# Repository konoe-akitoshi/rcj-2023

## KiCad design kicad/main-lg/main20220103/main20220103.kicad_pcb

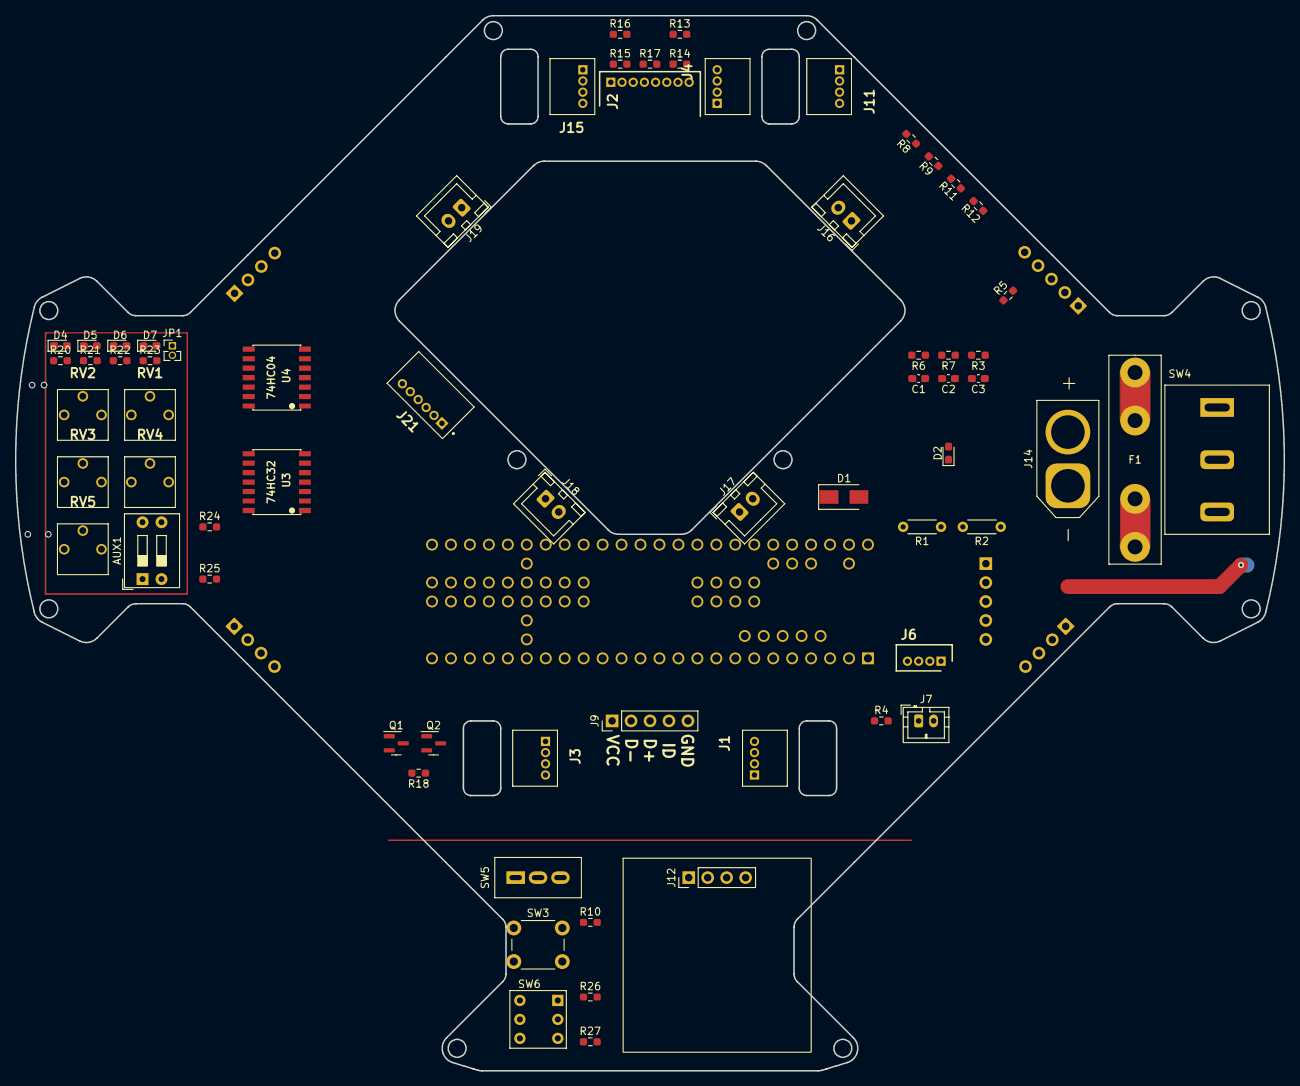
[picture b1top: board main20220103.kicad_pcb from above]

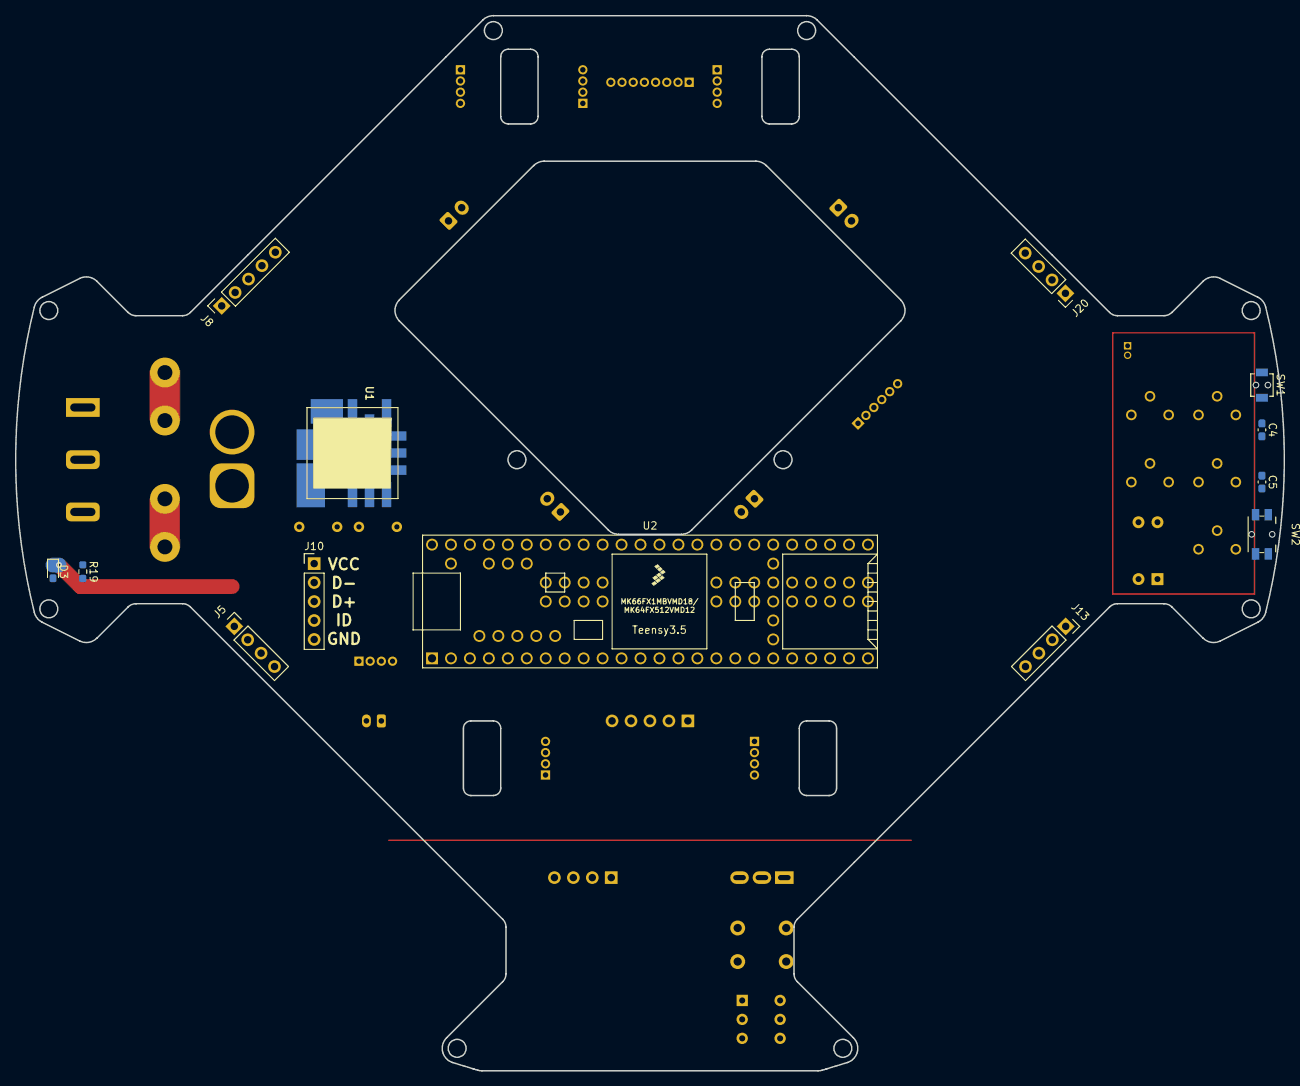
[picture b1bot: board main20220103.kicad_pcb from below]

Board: 2 copper layers, 170.0 x 141.4 mm, 80 parts (13 on the bottom side), 89 nets.

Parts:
AUX1: SW_DIP_x02; SW_DIP_SPSTx02_Slide_9.78x7.26mm_W7.62mm_P2.54mm
C1, C2, C3: 10u; C_0603_1608Metric_Pad1.08x0.95mm_HandSolder
C4, C5: 0.1u; C_0603_1608Metric_Pad1.08x0.95mm_HandSolder
D1: SX34F; D_SMA
D2, D3: LED; LED_SMLE13WBC8W1
D4: LED1_R; LED_SMLE13WBC8W1
D5: LED2_G; LED_SMLE13WBC8W1
D6: LED3_Y; LED_SMLE13WBC8W1
D7: LED4_B; LED_SMLE13WBC8W1
F1: Fuse 15A; FUSE_20mm
J1: MD2; JSTS4B-ZRLFSN
J2: MD4; JSTS4B-ZRLFSN
J3: MD3; JSTS4B-ZRLFSN
J4: MD1; JSTS4B-ZRLFSN
J5: XBee; PinSocket_1x04_P2.54mm_Vertical
J6: Serial3/Vision; JSTB4B-ZR
J7: raspi-power; JST_PH_B2B-PH-K_1x02_P2.00mm_Vertical
J8: Serial2/IMU; PinSocket_1x05_P2.54mm_Vertical
J9: micro-b_out; PinHeader_1x05_P2.54mm_Vertical
J10: micro-b_in; PinHeader_1x05_P2.54mm_Vertical
J11: I2C_ToF; JSTS4B-ZRLFSN
J12: I2C_OLED; OLED
J13: drib-kick; PinSocket_1x04_P2.54mm_Vertical
J14: Power IN; AMASS_XT60-M_1x02_P7.20mm_Vertical
J15: LINE; JSTS8B-ZRLFSN
J16: MD1; JST_XH_B2B-XH-A_1x02_P2.50mm_Vertical
J17: MD2; JST_XH_B2B-XH-A_1x02_P2.50mm_Vertical
J18: MD3; JST_XH_B2B-XH-A_1x02_P2.50mm_Vertical
J19: MD4; JST_XH_B2B-XH-A_1x02_P2.50mm_Vertical
J20: Drib-Kick; PinSocket_1x04_P2.54mm_Vertical
J21: Trimmer; JSTS6B-ZRLFSN
JP1: Jumper_2_Bridged; PinHeader_1x02_P1.27mm_Vertical
Q1: AO3400A; SOT-23
Q2: AO3401A; SOT-23
R1: 1k; R_Axial_DIN0204_L3.6mm_D1.6mm_P5.08mm_Horizontal
R2: 330; R_Axial_DIN0204_L3.6mm_D1.6mm_P5.08mm_Horizontal
R3, R26, R27: 470; R_0603_1608Metric_Pad0.98x0.95mm_HandSolder
R4, R5, R7, R11, R12, R13, R14, R15, R16, R17, R18: 10k; R_0603_1608Metric_Pad0.98x0.95mm_HandSolder
R6, R8, R9, R10, R24, R25: 47k; R_0603_1608Metric_Pad0.98x0.95mm_HandSolder
R19: 3k; R_0603_1608Metric_Pad0.98x0.95mm_HandSolder
R20, R21, R22, R23: 120; R_0603_1608Metric_Pad0.98x0.95mm_HandSolder
RV1, RV2, RV3, RV4, RV5: 20K; Trim-GF063P
SW1: PROG; TVAF06-A020B-R
SW2: Reset; THAU13-AB-R
SW3: SET; SW_PUSH_6mm
SW4: SW_SPST; SW_SPST_POWER
SW5: GOAL; MFS101D-14-Z
SW6: START; SW_NKK_B-12CCPRM
U1: OKL-T_3-W12N-C; OKL-T3-W12N-C
U2: Teensy3.5; Teensy35_36_x
U3: 74HC32; SOP14W
U4: 74HC04; SOP14W

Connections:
+3V3: J15.7, R8.1, R9.1, R11.1, R12.1, R24.1, R25.1, SW5.1 (A), SW6.1 (A), SW6.5 (A), U2.51 (3.3V), U3.14 (VCC), U4.13, U4.14 (VCC)
+5V: C2.1, D1.2 (A), J5.2, J6.2, J7.1, J8.3, J11.2, J12.2, Q2.2 (S), R3.1, R10.1, R18.1, U1.4 (VOUT), U1.5 (SENSE)
+15V: C1.1, F1.1, J16.1, J17.1, J18.1, J19.1, J20.1, J20.3, R6.1, R19.1, U1.2 (VIN)
/AUX1/3: AUX1.3, R24.2, U2.68 (41)
/AUX1/4: AUX1.4, R25.2, U2.67 (40)
/LED/LED1: R20.1, U2.50 (23_A9_PWM_Touch)
/LED/LED2: R21.1, U2.49 (22_A8_PWM_Touch)
/LED/LED3: R22.1, U2.48 (21_A7_PWM_CS0_MOSI1)
/LED/LED4: R23.1, U2.47 (20_A6_PWM_CS0_SCK1)
/Switch/SW_GOAL: SW5.2 (B), U2.41 (14_A0_PWM_SCK0)
/Switch/SW_START: SW6.2 (B), U2.43 (16_A2_SCL0_Touch)
/Switch/SW_led_G: R27.1, U2.44 (17_A3_SDA0_Touch)
/Switch/SW_led_R: R26.1, U2.42 (15_A1_CS0_Touch)
GND: AUX1.1, AUX1.2, C1.2, C2.2, C3.2, C4.2, C5.1, D2.1 (K), D3.1 (K), J5.4, J6.4, J7.2, J8.5, J11.4, J12.4, J13.2, J13.4, J14.1, J15.8, J16.2, J17.2, J18.2, J19.2, J20.2, J20.4, JP1.1 (A), Q1.2 (S), R2.1, R7.2, SW1.2, SW2.2, SW3.2, SW5.3 (C), SW6.3 (C), U1.1 (ON/OFF), U1.3 (GND_1), U1.7 (GND_2), U2.1 (GND), U2.27 (GND), U2.39 (GND), U2.61 (GND), U2.62 (GND), U2.63 (G), U2.74 (GND), U3.7 (GND), U4.7 (GND)
unnamed: C5.2, R9.2, SW2.1, U2.29 (Reset)
unnamed: D1.1 (K), U2.53 (Vin)
unnamed: D2.2 (A), R3.2
unnamed: D3.2 (A), R19.2
unnamed: D4.1 (K), D5.1 (K), D6.1 (K), D7.1 (K), JP1.2 (B)
unnamed: D4.2 (A), R20.2
unnamed: D5.2 (A), R21.2
unnamed: D6.2 (A), R22.2
unnamed: D7.2 (A), R23.2
unnamed: F1.2, SW4.1 (A)
unnamed: J1.1, J1.3, U2.33 (36_A17_PWM)
unnamed: J1.2, U2.72 (45_MISO2)
unnamed: J1.4, U2.73 (46_SCK2)
unnamed: J2.1, J2.3, U2.35 (38_A19_PWM_SDA1)
unnamed: J2.2, U2.78 (49_A23)
unnamed: J2.4, U2.79 (50_A24)
unnamed: J3.1, J3.3, U2.34 (37_A18_PWM_SCL1)
unnamed: J3.2, U2.76 (47_RX6_SCL0)
unnamed: J3.4, U2.77 (48_TX6_SDA0)
unnamed: J4.1, J4.3, U2.32 (35_A16_PWM)
unnamed: J4.2, U2.70 (43_CS2)
unnamed: J4.4, U2.71 (44_MOSI2)
unnamed: J5.1, U2.3 (1_TX1_MISO1_Touch)
unnamed: J5.3, U2.2 (0_RX1_MOSI1_Touch)
unnamed: J6.1, U2.10 (8_TX3_MISO0_SDA0)
unnamed: J6.3, R4.2
unnamed: J8.1, R10.2, SW3.1
unnamed: J8.2, U2.12 (10_PWM_TX2_CS0)
unnamed: J8.4, R5.2
unnamed: J9.1, J10.1
unnamed: J9.2, J10.2
unnamed: J9.3, J10.3
unnamed: J9.4, J10.4
unnamed: J9.5, J10.5
unnamed: J11.1, J12.1, R11.2, U2.46 (19_A5_SCL0_Touch)
unnamed: J11.3, J12.3, R12.2, U2.45 (18_A4_SDA0_Touch)
unnamed: J13.1, U2.8 (6_PWM)
unnamed: J13.3, U2.13 (11_MOSI0)
unnamed: J14.2, SW4.2 (B)
unnamed: J15.1, R13.2
unnamed: J15.2, R14.2
unnamed: J15.3, R17.2
unnamed: J15.4, Q2.3 (D)
unnamed: J15.5, R15.2
unnamed: J15.6, R16.2
unnamed: J21.1, RV1.1, RV2.1, RV3.1, RV4.1, RV5.1
unnamed: J21.2, RV5.2, RV5.3
unnamed: J21.3, RV4.2, RV4.3
unnamed: J21.4, RV3.2, RV3.3
unnamed: J21.5, RV2.2, RV2.3
unnamed: J21.6, RV1.2, RV1.3
unnamed: Q1.1 (G), U2.22 (30_PWM_CAN0RX_Touch)
unnamed: Q1.3 (D), Q2.1 (G), R18.2
unnamed: R1.1, R2.2
unnamed: R1.2, U1.6 (TRIM)
unnamed: R4.1, U2.9 (7_RX3_MOSI0_SCL0)
unnamed: R5.1, U2.11 (9_PWM_RX2_CS0)
unnamed: R13.1, U2.37 (A21_DAC0), U4.1
unnamed: R14.1, U2.38 (A22_DAC1), U4.3
unnamed: R15.1, U2.59 (A26_D-), U4.9
unnamed: R16.1, U2.36 (39_A20), U4.11
unnamed: R17.1, U2.60 (A25_D+), U4.5
unnamed: R26.2, SW6.4 (KR)
unnamed: R27.2, SW6.6 (KG)
unnamed: U2.16 (24), U3.4, U4.2
unnamed: U2.17 (25), U3.9, U4.4
unnamed: U2.18 (26_TX1_SCL2), U3.5, U4.6
unnamed: U2.19 (27_RX1_SCK0), U3.10, U4.8
unnamed: U2.20 (28_MOSI0), U3.1, U4.10
unnamed: U2.21 (29_PWM_CAN0TX_Touch), U3.3
unnamed: U3.2, U3.11
unnamed: U3.6, U3.12
unnamed: U3.8, U3.13
PROG: C4.1, R8.2, SW1.1, U2.28 (Program)
Vbatt: C3.1, R6.2, R7.1, U2.30 (33_A14_TX5_CAN1TX_SCL0)

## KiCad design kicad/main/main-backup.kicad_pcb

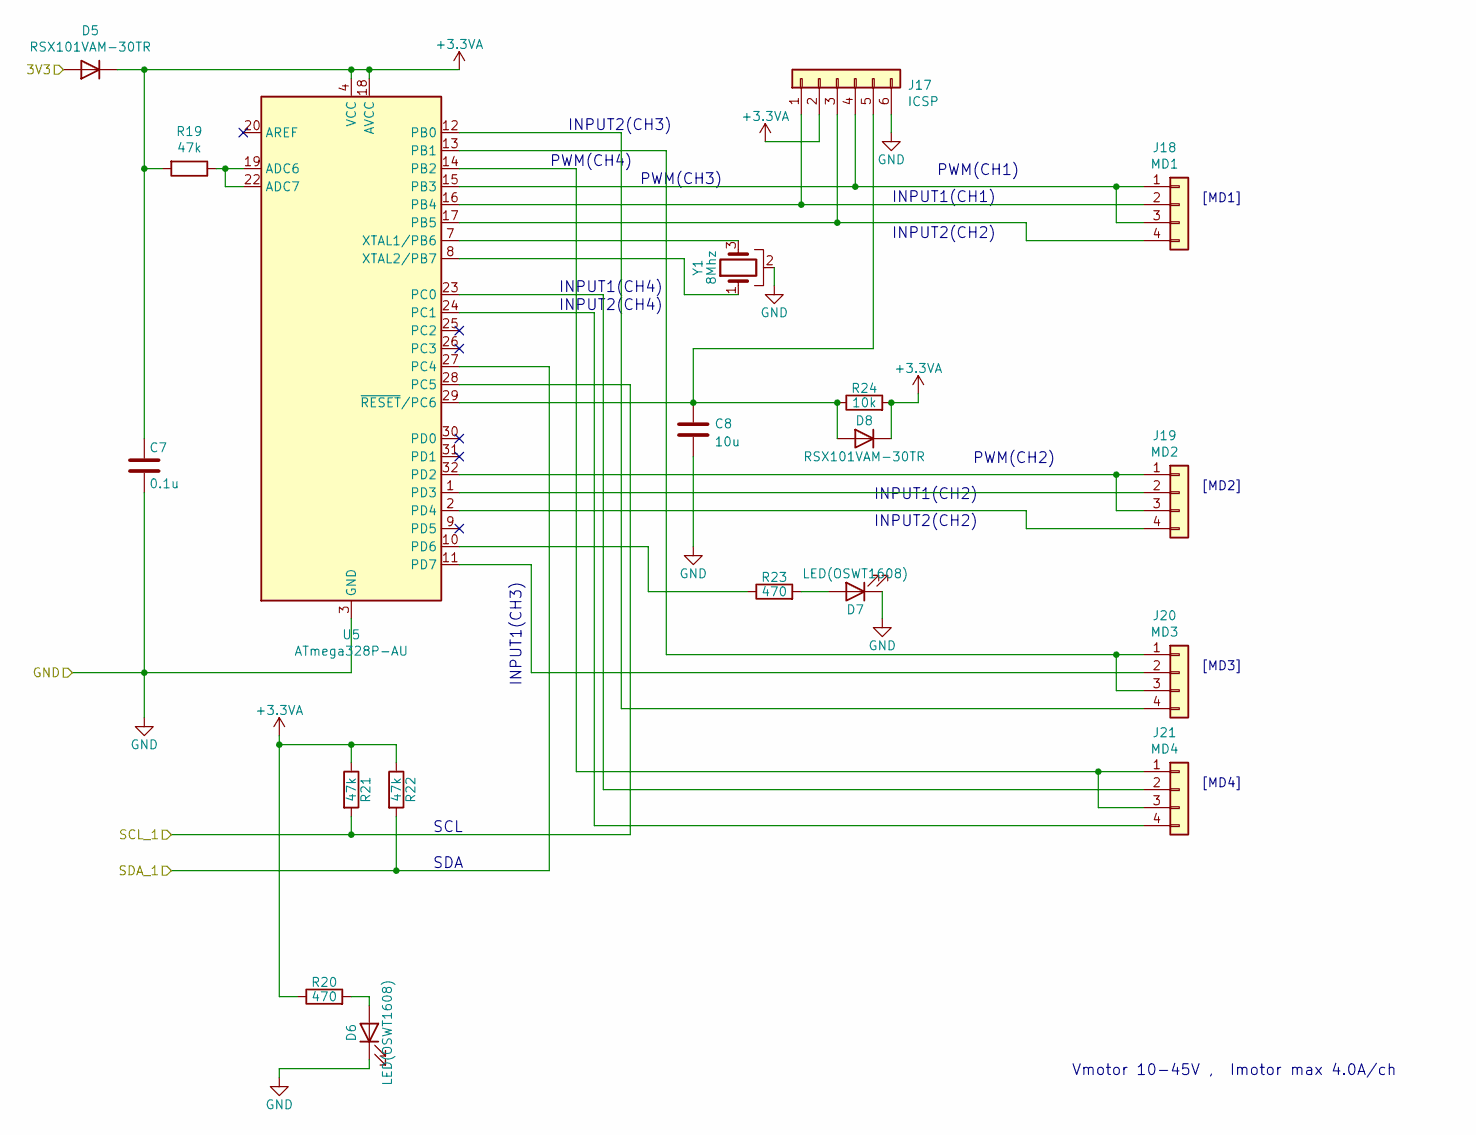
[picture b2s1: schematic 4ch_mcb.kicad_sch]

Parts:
C7: 0.1u; C_0603_1608Metric_Pad1.08x0.95mm_HandSolder
C8: 10u; C_0603_1608Metric_Pad1.08x0.95mm_HandSolder
D5, D8: RSX101VAM-30TR; D_0805_2012Metric_Pad1.15x1.40mm_HandSolder
D6, D7: LED(OSWT1608); LED_0603_1608Metric_Pad1.05x0.95mm_HandSolder
J17: ICSP; JSTB6B-ZR
J18: MD1; JSTB4B-ZR
J19: MD2; JSTB4B-ZR
J20: MD3; JSTB4B-ZR
J21: MD4; JSTB4B-ZR
R19, R21, R22: 47k; R_0603_1608Metric_Pad0.98x0.95mm_HandSolder
R20, R23: 470; R_0603_1608Metric_Pad0.98x0.95mm_HandSolder
R24: 10k; R_0603_1608Metric_Pad0.98x0.95mm_HandSolder
U5: ATmega328P-AU; TQFP-32_7x7mm_P0.8mm
Y1: 8Mhz; Resonator-3Pin_W6.0mm_H3.0mm

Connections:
+3.3VA: C7.1, D5.1 (K), D8.1 (K), J17.2, R19.2, R20.1, R21.1, R22.1, R24.2, U5.4 (VCC), U5.6 (VCC), U5.18 (AVCC)
/Sheet63625160/SCL_1: R21.2, U5.28 (PC5); also elsewhere on the board
/Sheet63625160/SDA_1: R22.2, U5.27 (PC4); also elsewhere on the board
unnamed: C8.1, D8.2 (A), J17.5, R24.1, U5.29 (~RESET/PC6)
unnamed: D6.2 (A), R20.2
unnamed: D7.2 (A), R23.2
unnamed: J17.1, J18.2, U5.16 (PB4)
unnamed: J17.3, J18.4, U5.17 (PB5)
unnamed: J17.4, J18.1, J18.3, U5.15 (PB3)
unnamed: J19.1, J19.3, U5.32 (PD2)
unnamed: J19.2, U5.1 (PD3)
unnamed: J19.4, U5.2 (PD4)
unnamed: J20.1, J20.3, U5.13 (PB1)
unnamed: J20.2, U5.11 (PD7)
unnamed: J20.4, U5.12 (PB0)
unnamed: J21.1, J21.3, U5.14 (PB2)
unnamed: J21.2, U5.23 (PC0)
unnamed: J21.4, U5.24 (PC1)
unnamed: R19.1, U5.19 (ADC6), U5.22 (ADC7)
unnamed: R23.1, U5.10 (PD6)
unnamed: U5.7 (XTAL1/PB6), Y1.3
unnamed: U5.8 (XTAL2/PB7), Y1.1
SW1_3: D5.2 (A); also elsewhere on the board
SW1_6: C7.2, C8.2, D6.1 (K), D7.1 (K), J17.6, U5.3 (GND), U5.5 (GND), U5.21 (GND), Y1.2; also elsewhere on the board

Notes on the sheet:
INPUT2(CH3)
INPUT2(CH2)
PWM(CH1)
PWM(CH3)
PWM(CH2)
INPUT1(CH2)
INPUT1(CH4)
[MD2]
INPUT1(CH3)
[MD4]
INPUT2(CH4)
PWM(CH4)
[MD1]
SDA
[MD3]
Vmotor 10-45V , Imotor max 4.0A/ch
SCL
INPUT1(CH1)

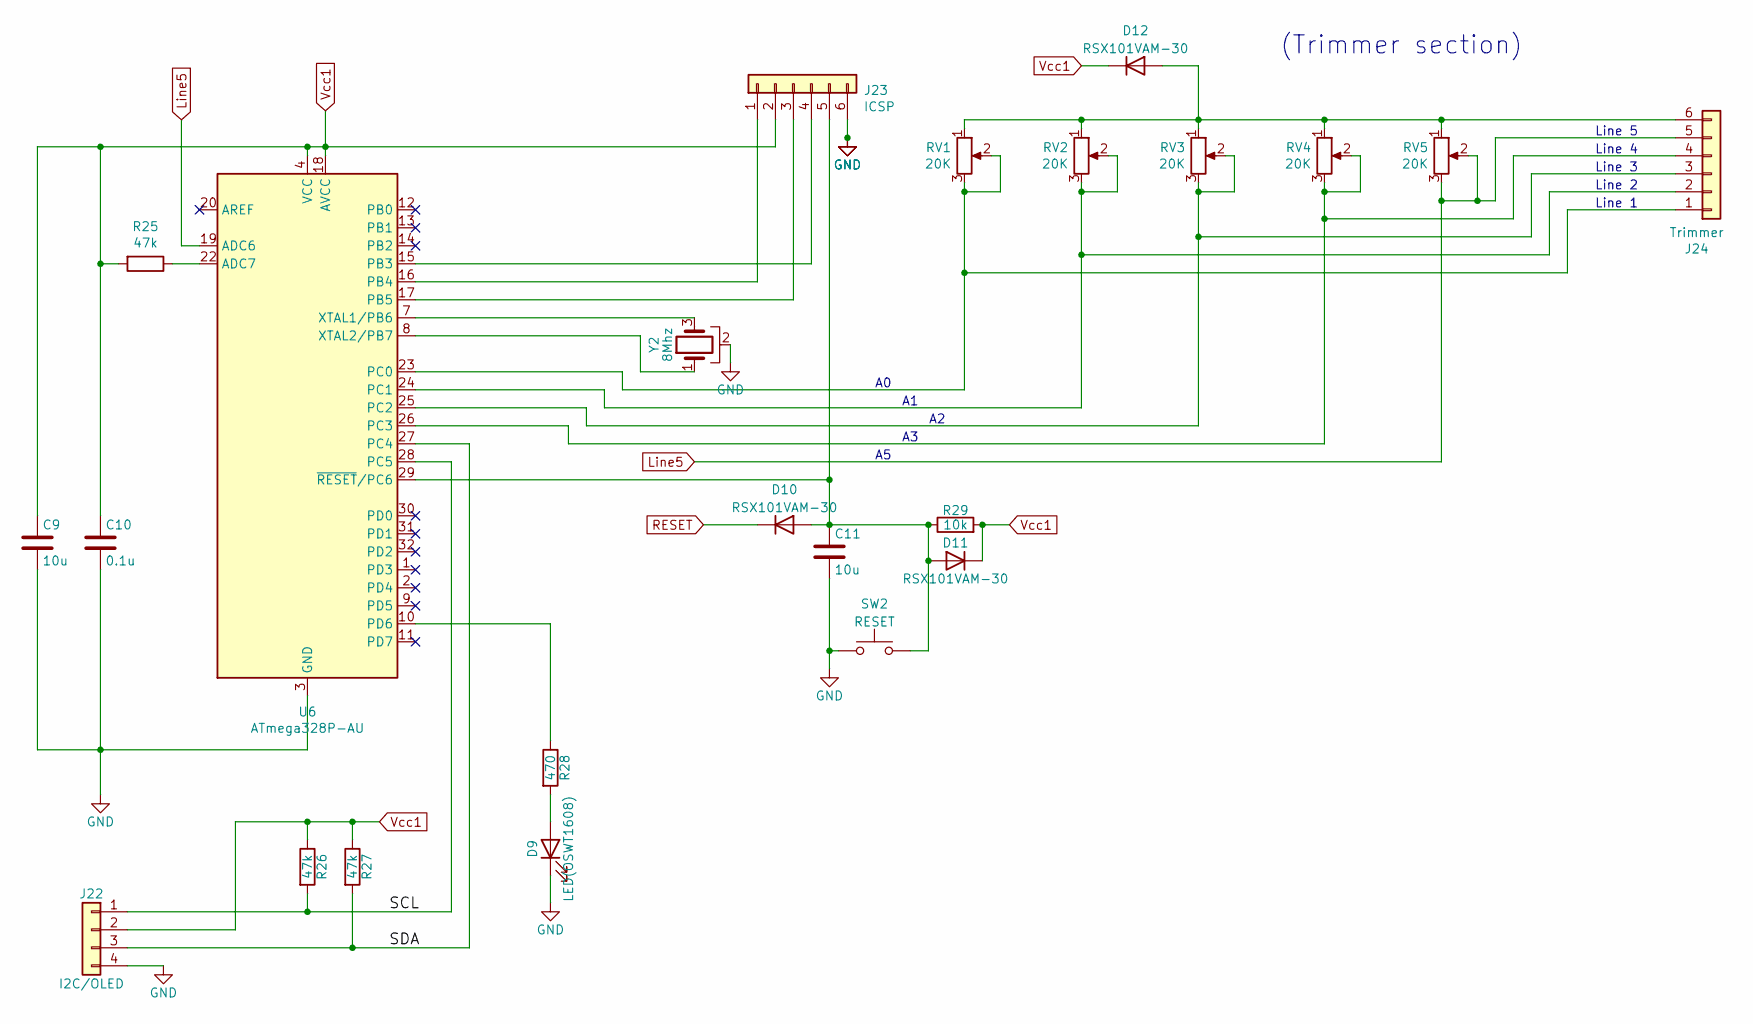
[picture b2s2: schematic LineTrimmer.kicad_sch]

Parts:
C9, C11: 10u; C_0603_1608Metric_Pad1.08x0.95mm_HandSolder
C10: 0.1u; C_0603_1608Metric_Pad1.08x0.95mm_HandSolder
D9: LED(OSWT1608); LED_SMLE13WBC8W1
D10, D11, D12: RSX101VAM-30; D_0805_2012Metric_Pad1.15x1.40mm_HandSolder
J22: I2C/OLED; JSTB4B-ZR
J23: ICSP; JSTB6B-ZR
J24: Trimmer; JSTB6B-ZR
R25, R26, R27: 47k; R_0603_1608Metric_Pad0.98x0.95mm_HandSolder
R28: 470; R_0603_1608Metric_Pad0.98x0.95mm_HandSolder
R29: 10k; R_0603_1608Metric_Pad0.98x0.95mm_HandSolder
RV1, RV2, RV3, RV4, RV5: 20K; Trim-GF063P
SW2: RESET; TVAF06-A020B-R
U6: ATmega328P-AU; TQFP-32_7x7mm_P0.8mm
Y2: 8Mhz; Resonator-3Pin_W6.0mm_H3.0mm

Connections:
/LineTrimmer/SCL: J22.1, R26.2, U6.28 (PC5)
/LineTrimmer/SDA: J22.3, R27.2, U6.27 (PC4)
Line5: J24.5, RV5.2, RV5.3, U6.19 (ADC6)
unnamed: C11.1, D10.2 (A), D11.2 (A), J23.5, R29.1, SW2.2, U6.29 (~RESET/PC6)
unnamed: D9.2 (A), R28.2
unnamed: D12.2 (A), J24.6, RV1.1, RV2.1, RV3.1, RV4.1, RV5.1
unnamed: J23.1, U6.16 (PB4)
unnamed: J23.3, U6.17 (PB5)
unnamed: J23.4, U6.15 (PB3)
unnamed: J24.1, RV1.2, RV1.3, U6.23 (PC0)
unnamed: J24.2, RV2.2, RV2.3, U6.24 (PC1)
unnamed: J24.3, RV3.2, RV3.3, U6.25 (PC2)
unnamed: J24.4, RV4.2, RV4.3, U6.26 (PC3)
unnamed: R25.1, U6.22 (ADC7)
unnamed: R28.1, U6.10 (PD6)
unnamed: U6.7 (XTAL1/PB6), Y2.3
unnamed: U6.8 (XTAL2/PB7), Y2.1
RESET: D10.1 (K); also elsewhere on the board
SW1_6: C9.2, C10.2, C11.2, D9.1 (K), J22.4, J23.6, SW2.1, U6.3 (GND), U6.5 (GND), U6.21 (GND), Y2.2; also elsewhere on the board
Vcc1: C9.1, C10.1, D11.1 (K), D12.1 (K), J22.2, J23.2, R25.2, R26.1, R27.1, R29.2, U6.4 (VCC), U6.6 (VCC), U6.18 (AVCC)

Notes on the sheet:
Line 1
Line 2
Line 3
(Trimmer section)
Line 4
Line 5

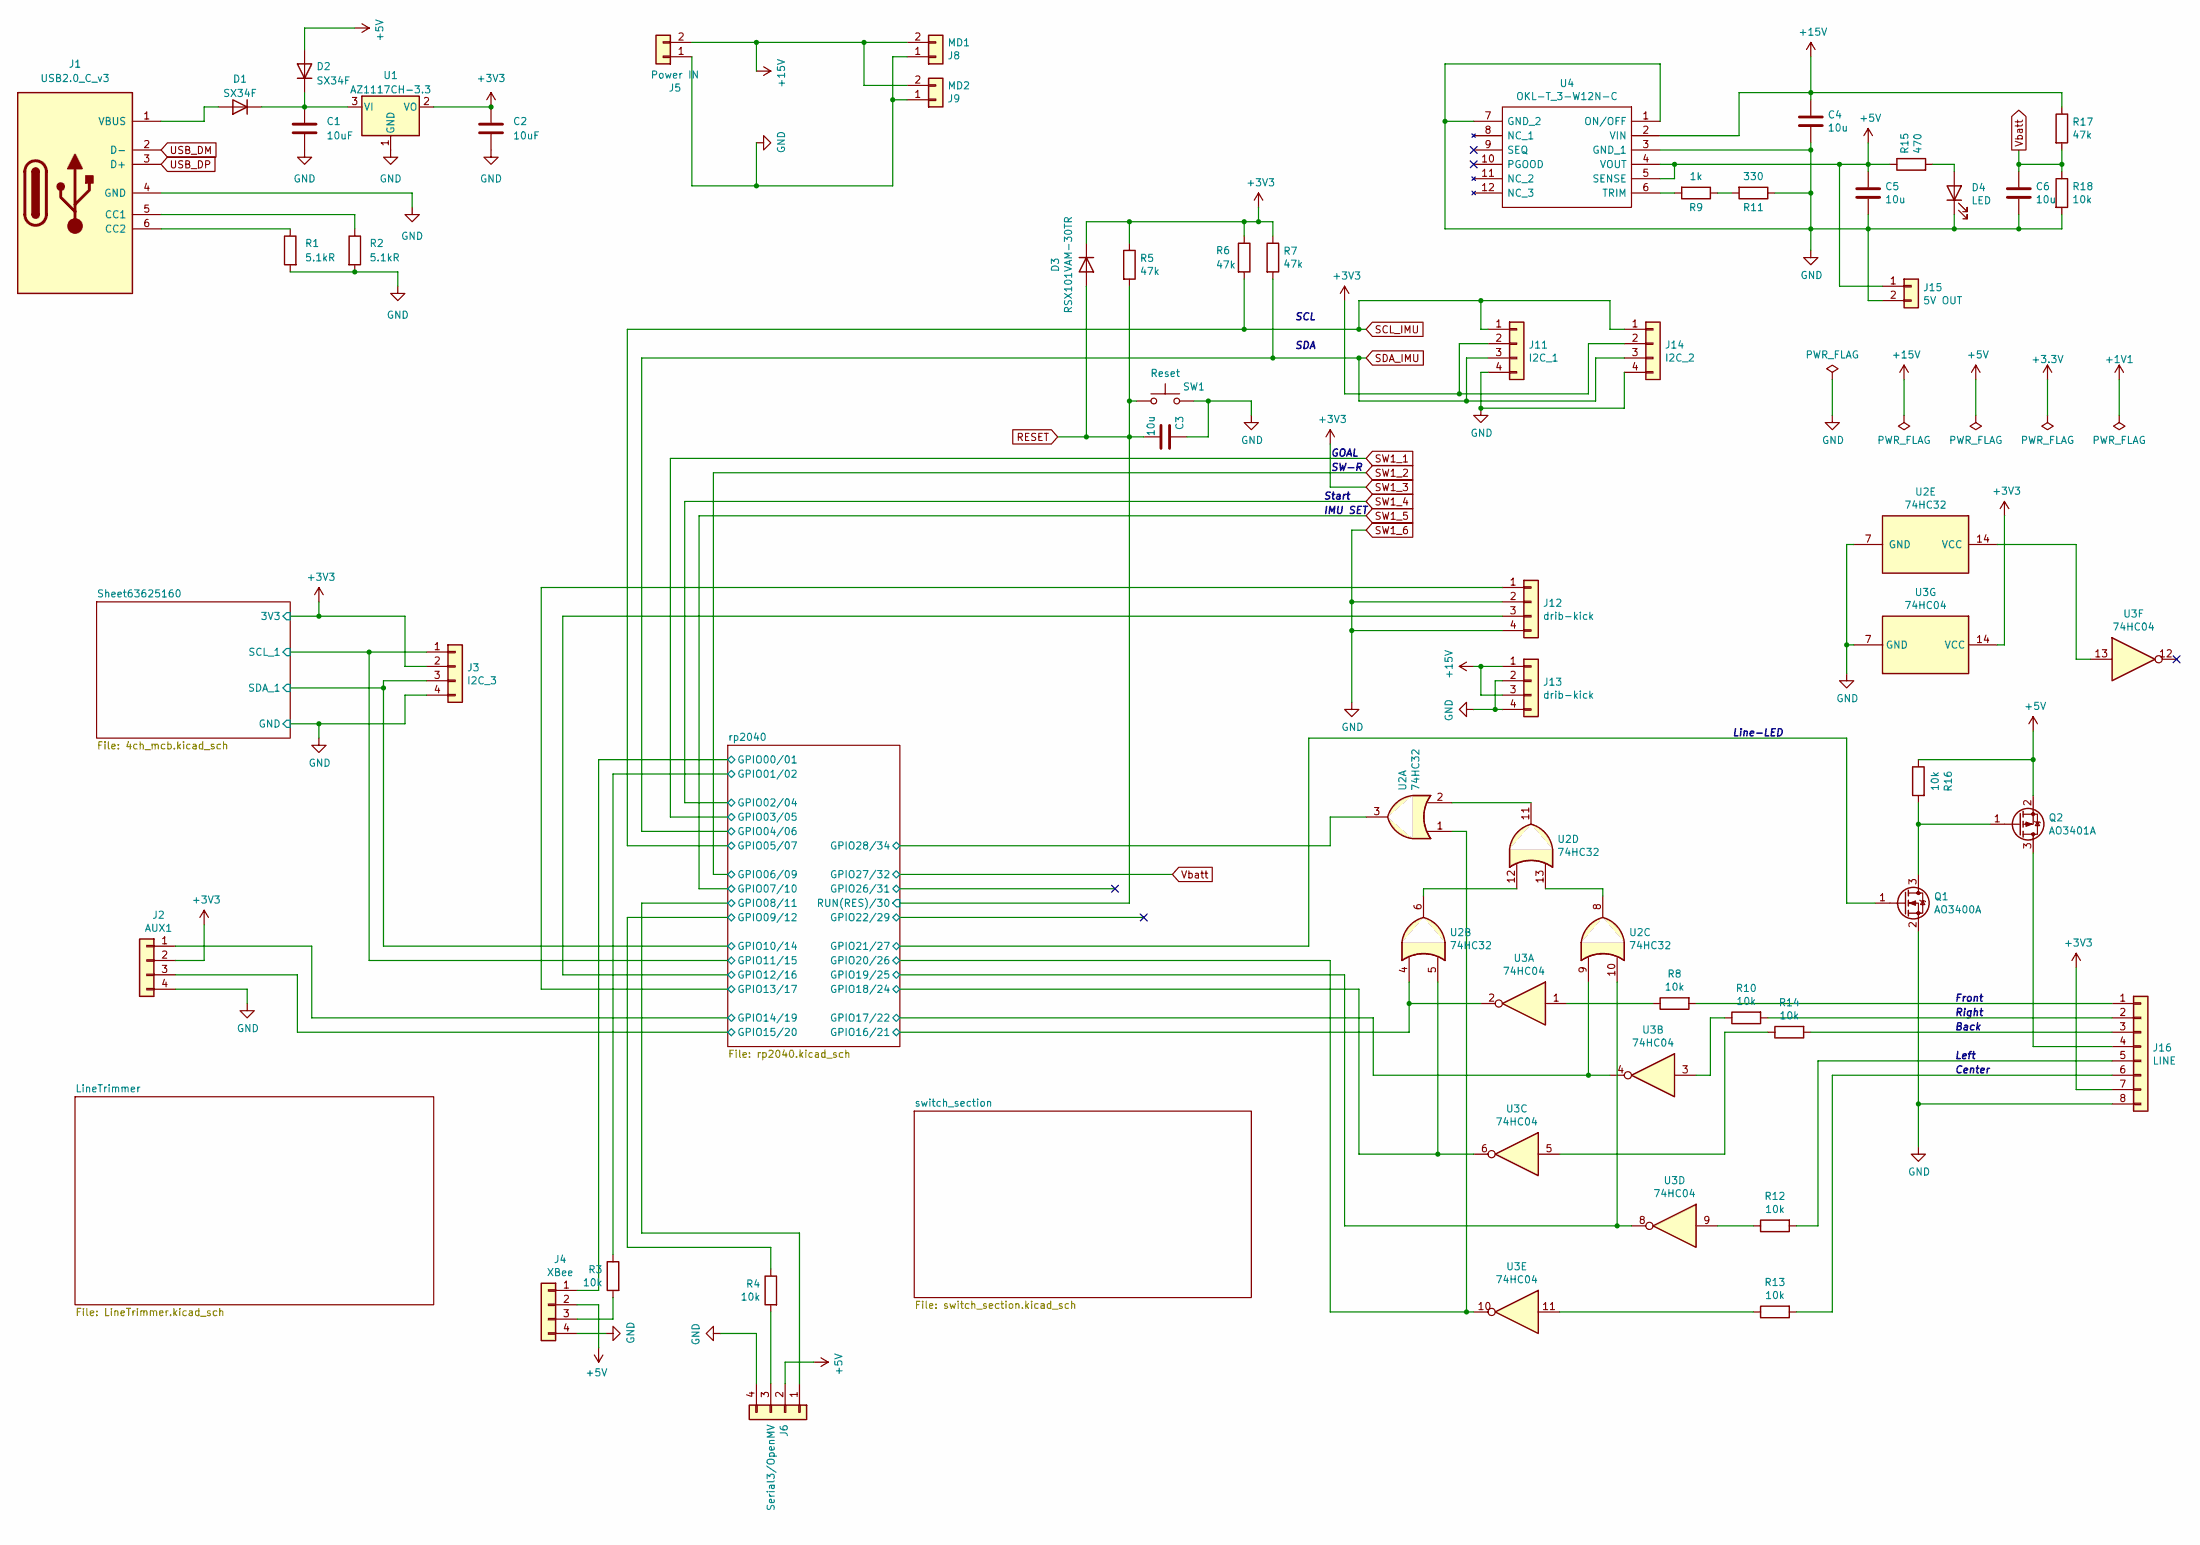
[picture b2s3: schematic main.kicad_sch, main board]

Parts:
C1, C2: 10uF; C_0603_1608Metric_Pad1.08x0.95mm_HandSolder
C3, C4, C5, C6: 10u; C_0603_1608Metric_Pad1.08x0.95mm_HandSolder
D1, D2: SX34F; D_SMA
D3: RSX101VAM-30TR; D_SMA
D4: LED; LED_SMLE13WBC8W1
J1: USB2.0_C_v3; USB-C-12-Pin-MidMount-ali-v4
J2: AUX1; JSTB4B-ZR
J3: I2C_3; JSTB4B-ZR
J4: XBee; PinHeader_1x04_P2.54mm_Vertical
J5: Power IN; JST_VH_B2P-VH-B_1x02_P3.96mm_Vertical
J6: Serial3/OpenMV; JSTB4B-ZR
J8: MD1; JST_XH_S2B-XH-A-1_1x02_P2.50mm_Horizontal
J9: MD2; JST_XH_S2B-XH-A-1_1x02_P2.50mm_Horizontal
J11: I2C_1; JSTB4B-ZR
J12, J13: drib-kick; PinHeader_1x04_P2.54mm_Vertical
J14: I2C_2; JSTB4B-ZR
J15: 5V OUT; JST_XH_B2B-XH-A_1x02_P2.50mm_Vertical
J16: LINE; JSTB8B-ZR
Q1: AO3400A; SOT-23_Handsoldering
Q2: AO3401A; SOT-23_Handsoldering
R1, R2: 5.1kR; R_0603_1608Metric_Pad0.98x0.95mm_HandSolder
R3, R4, R8, R10, R12, R13, R14, R16, R18: 10k; R_0603_1608Metric_Pad0.98x0.95mm_HandSolder
R5, R6, R7, R17: 47k; R_0603_1608Metric_Pad0.98x0.95mm_HandSolder
R9: 1k; R_Axial_DIN0204_L3.6mm_D1.6mm_P5.08mm_Horizontal
R11: 330; R_Axial_DIN0204_L3.6mm_D1.6mm_P5.08mm_Horizontal
R15: 470; R_0603_1608Metric_Pad0.98x0.95mm_HandSolder
SW1: Reset; THAU13-AB-R
U1: AZ1117CH-3.3; SOT-223-3_TabPin2
U2: 74HC32; SOP14W
U3: 74HC04; SOP14W
U4: OKL-T_3-W12N-C; OKL-T3-W12N-C; Manufacturer_Part_Number OKL-T/6-W12N-C; Mouser Part Number 580-OKL-T/6-W12N-C

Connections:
+5V: C5.1, D2.2 (A), J4.2, J6.2, J15.1, Q2.2 (S), R15.1, R16.1, U4.4 (VOUT), U4.5 (SENSE); also elsewhere on the board
+15V: C4.1, J5.2, J8.2, J9.2, J13.1, J13.3, R17.1, U4.2 (VIN)
/Sheet63625160/SCL_1: J3.1; also elsewhere on the board
/Sheet63625160/SDA_1: J3.3; also elsewhere on the board
/rp2040/GPIO00/01: J4.1; also elsewhere on the board
/rp2040/GPIO01/02: R3.1; also elsewhere on the board
/rp2040/GPIO08/11: J6.1; also elsewhere on the board
/rp2040/GPIO09/12: R4.1; also elsewhere on the board
/rp2040/GPIO12/16: J12.3; also elsewhere on the board
/rp2040/GPIO13/17: J12.1; also elsewhere on the board
/rp2040/GPIO14/19: J2.1; also elsewhere on the board
/rp2040/GPIO15/20: J2.3; also elsewhere on the board
/rp2040/GPIO16/21: U2.4, U3.2; also elsewhere on the board
/rp2040/GPIO17/22: U2.9, U3.4; also elsewhere on the board
/rp2040/GPIO18/24: U2.5, U3.6; also elsewhere on the board
/rp2040/GPIO19/25: U2.10, U3.8; also elsewhere on the board
/rp2040/GPIO20/26: U2.1, U3.10; also elsewhere on the board
/rp2040/GPIO21/27: Q1.1 (G); also elsewhere on the board
/rp2040/GPIO28/34: U2.3; also elsewhere on the board
unnamed: C1.1, D1.1 (K), D2.1 (K), U1.3 (VI)
unnamed: D1.2 (A), J1.1 (VBUS)
unnamed: D4.2 (A), R15.2
unnamed: J1.5 (CC1), R2.1
unnamed: J1.6 (CC2), R1.1
unnamed: J4.3, R3.2
unnamed: J6.3, R4.2
unnamed: J16.1, R8.2
unnamed: J16.2, R10.2
unnamed: J16.3, R14.2
unnamed: J16.4, Q2.3 (D)
unnamed: J16.5, R12.2
unnamed: J16.6, R13.2
unnamed: Q1.3 (D), Q2.1 (G), R16.2
unnamed: R8.1, U3.1
unnamed: R9.2, U4.6 (TRIM)
unnamed: R10.1, U3.3
unnamed: R9.1, R11.2
unnamed: R12.1, U3.9
unnamed: R13.1, U3.11
unnamed: R14.1, U3.5
unnamed: U2.2, U2.11
unnamed: U2.6, U2.12
unnamed: U2.8, U2.13
unnamed: U2.14 (VCC), U3.13
RESET: C3.2, D3.2 (A), R5.2, SW1.1; also elsewhere on the board
SCL_IMU: J11.1, J14.1, R6.2; also elsewhere on the board
SDA_IMU: J11.3, J14.3, R7.2; also elsewhere on the board
SW1_3: C2.1, D3.1 (K), J2.2, J3.2, J11.2, J14.2, J16.7, R5.1, R6.1, R7.1, U1.2 (VO), U3.14 (VCC); also elsewhere on the board
SW1_6: C1.2, C2.2, C3.1, C4.2, C5.2, C6.2, D4.1 (K), J1.4 (GND), J2.4, J3.4, J4.4, J5.1, J6.4, J8.1, J9.1, J11.4, J12.2, J12.4, J13.2, J13.4, J14.4, J15.2, J16.8, Q1.2 (S), R1.2, R2.2, R11.1, R18.2, SW1.2, U1.1 (GND), U2.7 (GND), U3.7 (GND), U4.1 (ON/OFF), U4.3 (GND_1), U4.7 (GND_2); also elsewhere on the board
USB_DM: J1.2 (D-); also elsewhere on the board
USB_DP: J1.3 (D+); also elsewhere on the board
Vbatt: C6.1, R17.2, R18.1; also elsewhere on the board

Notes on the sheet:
GOAL
Line-LED
Front
SCL
Back
IMU SET
Left
Center
SDA
Start
Right
SW-R

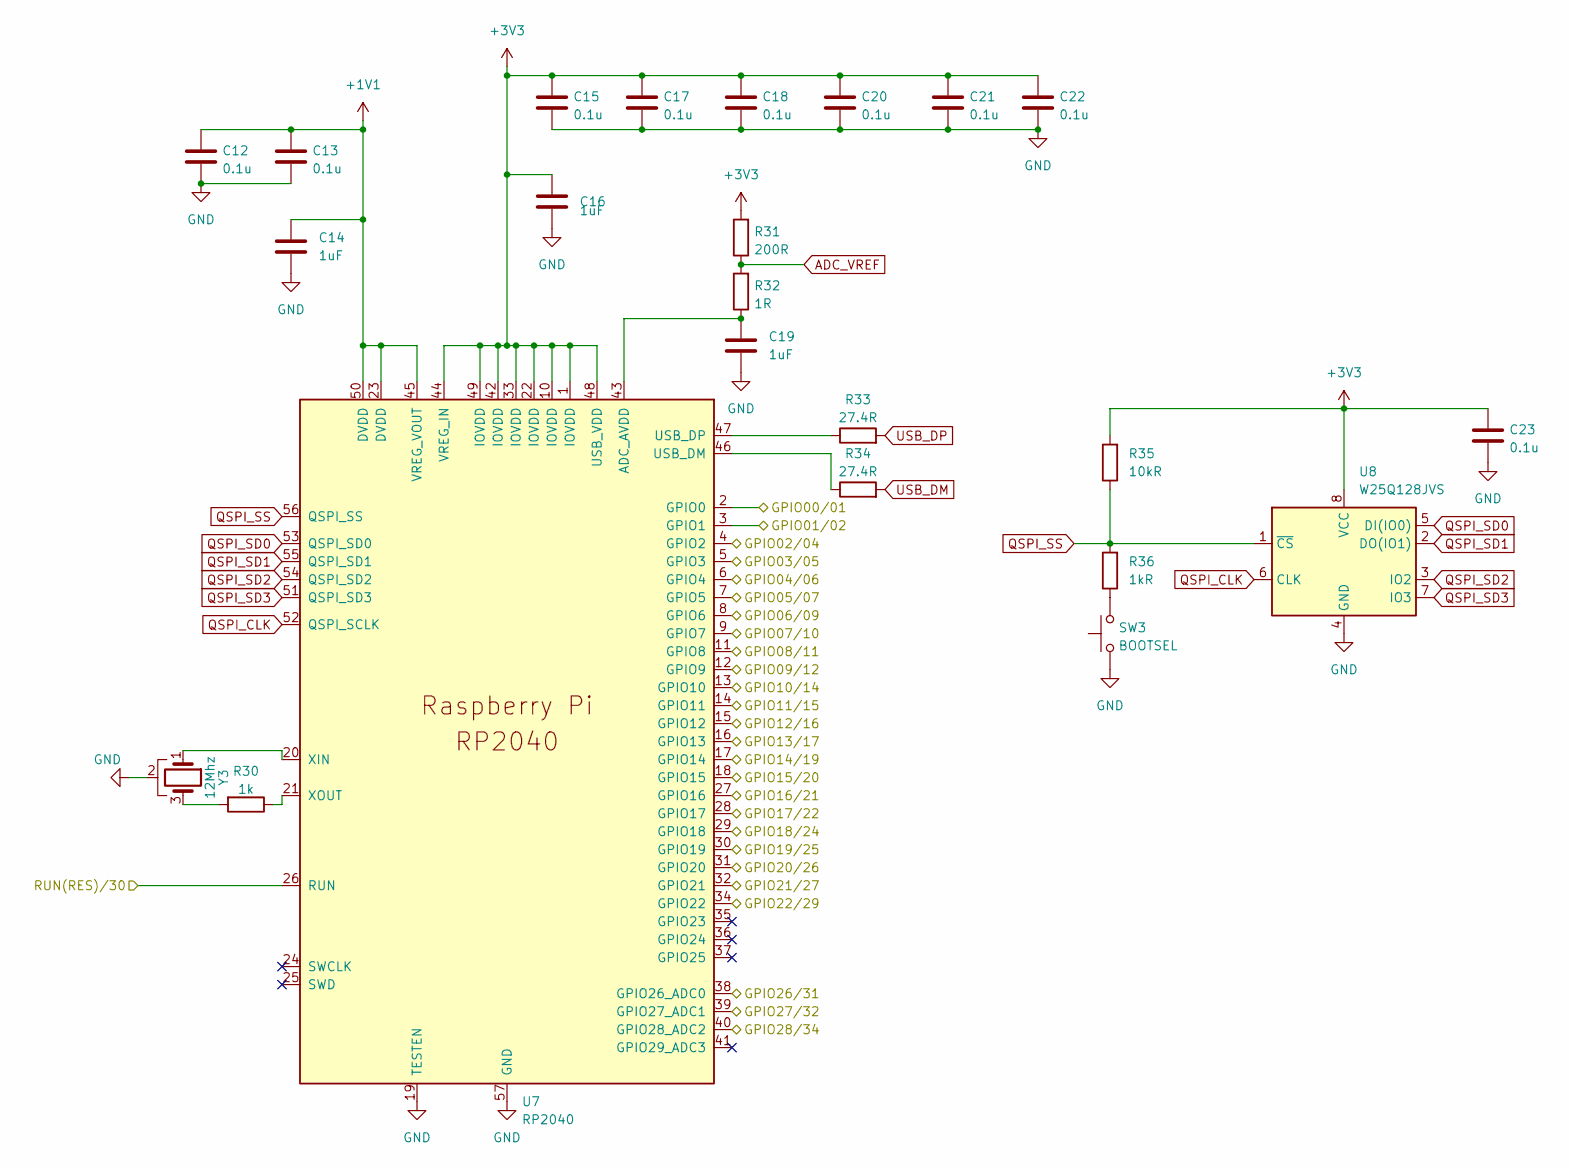
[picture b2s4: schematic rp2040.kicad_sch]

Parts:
C12, C13, C15, C17, C18, C20, C21, C22, C23: 0.1u; C_0603_1608Metric_Pad1.08x0.95mm_HandSolder
C14, C16, C19: 1uF; C_0603_1608Metric_Pad1.08x0.95mm_HandSolder
R30: 1k; R_0603_1608Metric_Pad0.98x0.95mm_HandSolder
R31: 200R; R_0603_1608Metric_Pad0.98x0.95mm_HandSolder
R32: 1R; R_0603_1608Metric_Pad0.98x0.95mm_HandSolder
R33, R34: 27.4R; R_0603_1608Metric_Pad0.98x0.95mm_HandSolder
R35: 10kR; R_0603_1608Metric_Pad0.98x0.95mm_HandSolder
R36: 1kR; R_0603_1608Metric_Pad0.98x0.95mm_HandSolder
SW3: BOOTSEL; TVAF06-A020B-R
U7: RP2040; RP2040_hand
U8: W25Q128JVS; W25Q16-128JV-SOIC
Y3: 12Mhz; Resonator-3Pin_W6.0mm_H3.0mm

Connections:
+1V1: C12.1, C13.1, C14.1, U7.23 (DVDD), U7.45 (VREG_VOUT), U7.50 (DVDD)
/Sheet63625160/SCL_1: U7.14 (GPIO11); also elsewhere on the board
/Sheet63625160/SDA_1: U7.13 (GPIO10); also elsewhere on the board
/rp2040/GPIO00/01: U7.2 (GPIO0); also elsewhere on the board
/rp2040/GPIO01/02: U7.3 (GPIO1); also elsewhere on the board
/rp2040/GPIO08/11: U7.11 (GPIO8); also elsewhere on the board
/rp2040/GPIO09/12: U7.12 (GPIO9); also elsewhere on the board
/rp2040/GPIO12/16: U7.15 (GPIO12); also elsewhere on the board
/rp2040/GPIO13/17: U7.16 (GPIO13); also elsewhere on the board
/rp2040/GPIO14/19: U7.17 (GPIO14); also elsewhere on the board
/rp2040/GPIO15/20: U7.18 (GPIO15); also elsewhere on the board
/rp2040/GPIO16/21: U7.27 (GPIO16); also elsewhere on the board
/rp2040/GPIO17/22: U7.28 (GPIO17); also elsewhere on the board
/rp2040/GPIO18/24: U7.29 (GPIO18); also elsewhere on the board
/rp2040/GPIO19/25: U7.30 (GPIO19); also elsewhere on the board
/rp2040/GPIO20/26: U7.31 (GPIO20); also elsewhere on the board
/rp2040/GPIO21/27: U7.32 (GPIO21); also elsewhere on the board
/rp2040/GPIO22/29: U7.34 (GPIO22)
/rp2040/GPIO26/31: U7.38 (GPIO26_ADC0)
/rp2040/GPIO28/34: U7.40 (GPIO28_ADC2); also elsewhere on the board
ADC_VREF: R31.1, R32.2
unnamed: C19.1, R32.1, U7.43 (ADC_AVDD)
unnamed: R30.1, U7.21 (XOUT)
unnamed: R30.2, Y3.3
unnamed: R33.1, U7.47 (USB_DP)
unnamed: R34.1, U7.46 (USB_DM)
unnamed: R36.1, SW3.2
unnamed: U7.20 (XIN), Y3.1
QSPI_CLK: U7.52 (QSPI_SCLK), U8.6 (CLK)
QSPI_SD0: U7.53 (QSPI_SD0), U8.5 (DI(IO0))
QSPI_SD1: U7.55 (QSPI_SD1), U8.2 (DO(IO1))
QSPI_SD2: U7.54 (QSPI_SD2), U8.3 (IO2)
QSPI_SD3: U7.51 (QSPI_SD3), U8.7 (IO3)
QSPI_SS: R35.1, R36.2, U7.56 (QSPI_SS), U8.1 (~CS)
RESET: U7.26 (RUN); also elsewhere on the board
SCL_IMU: U7.7 (GPIO5); also elsewhere on the board
SDA_IMU: U7.6 (GPIO4); also elsewhere on the board
SW1_1: U7.5 (GPIO3); also elsewhere on the board
SW1_2: U7.8 (GPIO6)
SW1_3: C15.1, C16.1, C17.1, C18.1, C20.1, C21.1, C22.1, C23.1, R31.2, R35.2, U7.1 (IOVDD), U7.10 (IOVDD), U7.22 (IOVDD), U7.33 (IOVDD), U7.42 (IOVDD), U7.44 (VREG_IN), U7.48 (USB_VDD), U7.49 (IOVDD), U8.8 (VCC); also elsewhere on the board
SW1_4: U7.4 (GPIO2); also elsewhere on the board
SW1_5: U7.9 (GPIO7); also elsewhere on the board
SW1_6: C12.2, C13.2, C14.2, C15.2, C16.2, C17.2, C18.2, C19.2, C20.2, C21.2, C22.2, C23.2, SW3.1, U7.19 (TESTEN), U7.57 (GND), U8.4 (GND), Y3.2; also elsewhere on the board
USB_DM: R34.2; also elsewhere on the board
USB_DP: R33.2; also elsewhere on the board
Vbatt: U7.39 (GPIO27_ADC1); also elsewhere on the board
